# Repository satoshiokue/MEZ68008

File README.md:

# MEZ68008
68008 Mezzanine board for EMUZ80 

R1 = 10k  
C1 = 0.1uF  
C2 = 47uF/16V  

https://github.com/satoshiokue/EMUZ80-68008

MEZ68008専用プリント基板 - オレンジピコショップ  
https://store.shopping.yahoo.co.jp/orangepicoshop/pico-a-061.html

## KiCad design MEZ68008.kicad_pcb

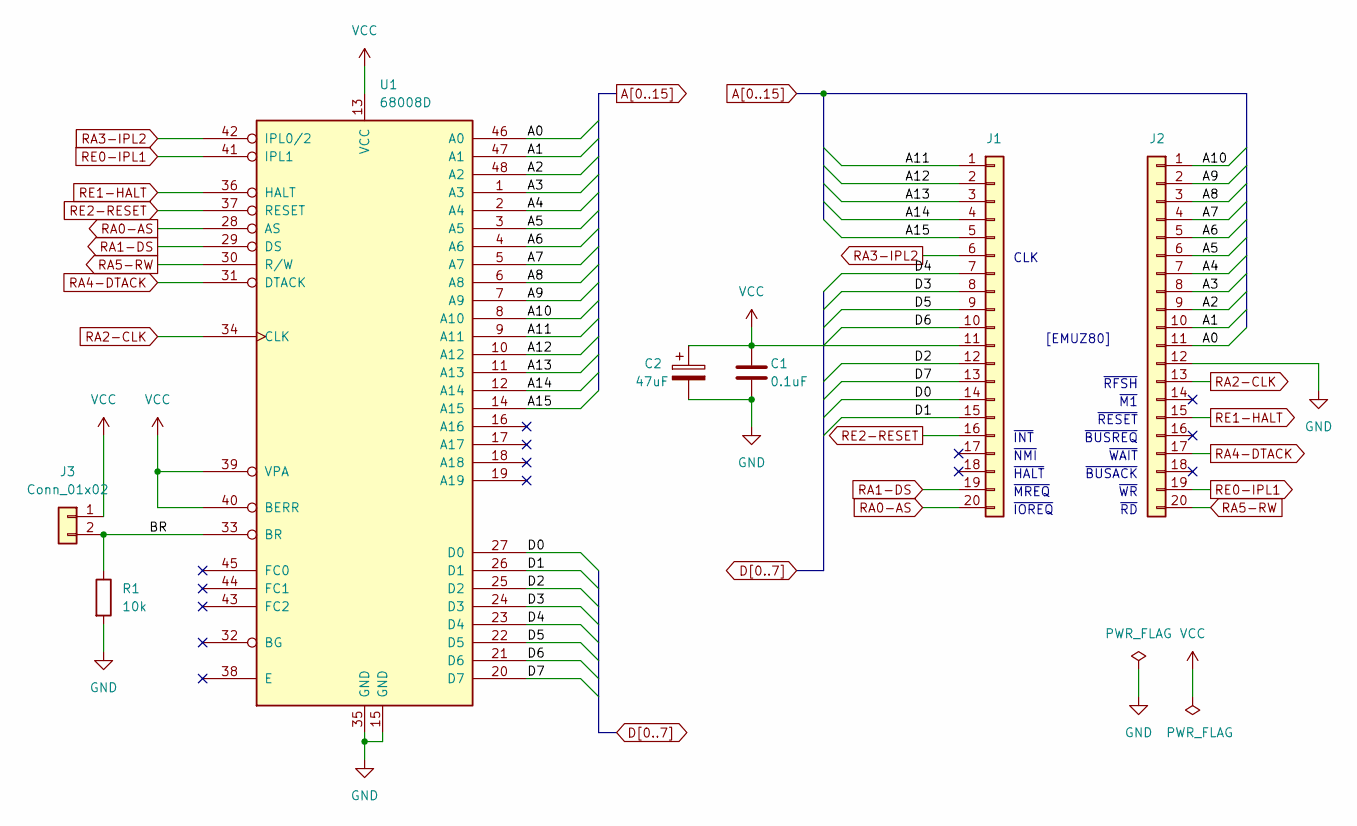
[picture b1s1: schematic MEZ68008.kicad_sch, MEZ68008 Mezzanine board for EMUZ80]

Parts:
C1: 0.1uF; C_Disc_D3.8mm_W2.6mm_P2.50mm
C2: 47uF; CP_Radial_D6.3mm_P2.50mm
J1, J2: Conn_01x20; PinHeader_1x20_P2.54mm_Vertical
J3: Conn_01x02; PinHeader_1x02_P2.54mm_Vertical
R1: 10k; R_Axial_DIN0207_L6.3mm_D2.5mm_P10.16mm_Horizontal
U1: 68008D; DIP-48_W15.24mm

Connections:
/BR: J3.2, R1.1, U1.33 (BR)
A0: J2.11, U1.46 (A0)
A1: J2.10, U1.47 (A1)
A2: J2.9, U1.48 (A2)
A3: J2.8, U1.1 (A3)
A4: J2.7, U1.2 (A4)
A5: J2.6, U1.3 (A5)
A6: J2.5, U1.4 (A6)
A7: J2.4, U1.5 (A7)
A8: J2.3, U1.6 (A8)
A9: J2.2, U1.7 (A9)
A10: J2.1, U1.8 (A10)
A11: J1.1, U1.9 (A11)
A12: J1.2, U1.10 (A12)
A13: J1.3, U1.11 (A13)
A14: J1.4, U1.12 (A14)
A15: J1.5, U1.14 (A15)
D0: J1.14, U1.27 (D0)
D1: J1.15, U1.26 (D1)
D2: J1.12, U1.25 (D2)
D3: J1.8, U1.24 (D3)
D4: J1.7, U1.23 (D4)
D5: J1.9, U1.22 (D5)
D6: J1.10, U1.21 (D6)
D7: J1.13, U1.20 (D7)
GND: C1.2, C2.2, J2.12, R1.2, U1.15 (GND), U1.35 (GND)
RA0-AS: J1.20, U1.28 (AS)
RA1-DS: J1.19, U1.29 (DS)
RA2-CLK: J2.13, U1.34 (CLK)
RA3-IPL2: J1.6, U1.42 (IPL0/2)
RA4-DTACK: J2.17, U1.31 (DTACK)
RA5-RW: J2.20, U1.30 (R/W)
RE0-IPL1: J2.19, U1.41 (IPL1)
RE1-HALT: J2.15, U1.36 (HALT)
RE2-RESET: J1.16, U1.37 (RESET)
VCC: C1.1, C2.1, J1.11, J3.1, U1.13 (VCC), U1.39 (VPA), U1.40 (BERR)

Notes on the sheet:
~{RFSH}
[EMUZ80]
~{NMI}
CLK
~{M1}
~{INT}
~{BUSREQ}
~{WAIT}
~{IOREQ}
~{BUSACK}
~{WR}
~{MREQ}
~{RESET}
~{HALT}
~{RD}

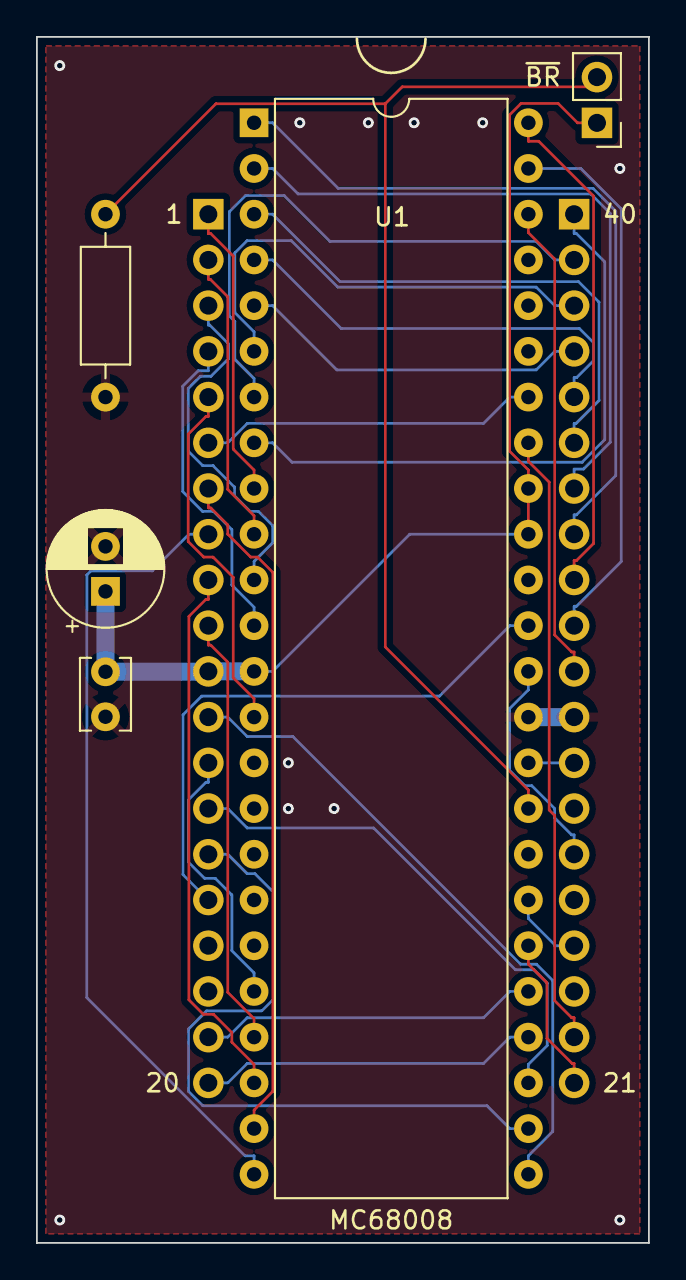
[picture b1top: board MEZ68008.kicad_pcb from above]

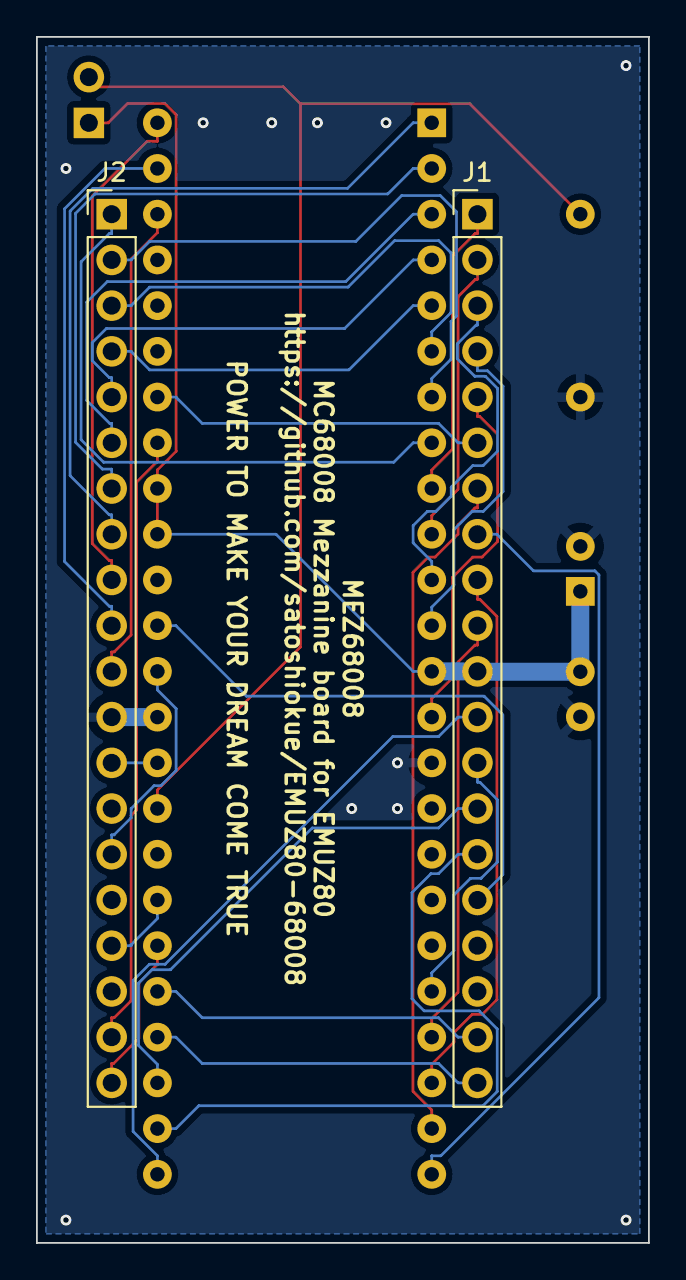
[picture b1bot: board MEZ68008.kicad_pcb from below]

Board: 2 copper layers, 34.0 x 67.0 mm, 7 parts (2 on the bottom side), 36 nets.

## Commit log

2022-10-17 Create foo
